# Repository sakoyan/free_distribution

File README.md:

# free_distribution
free circuit data for robocon

おでんの基板データ配布場所です。
一応完成版がアップされると思いますし、動作もすると思います。
不備などを見つけた方は@oden_umaruにビシバシとリプを飛ばしてください。
今までのデータを順次公開していきたいと思います。

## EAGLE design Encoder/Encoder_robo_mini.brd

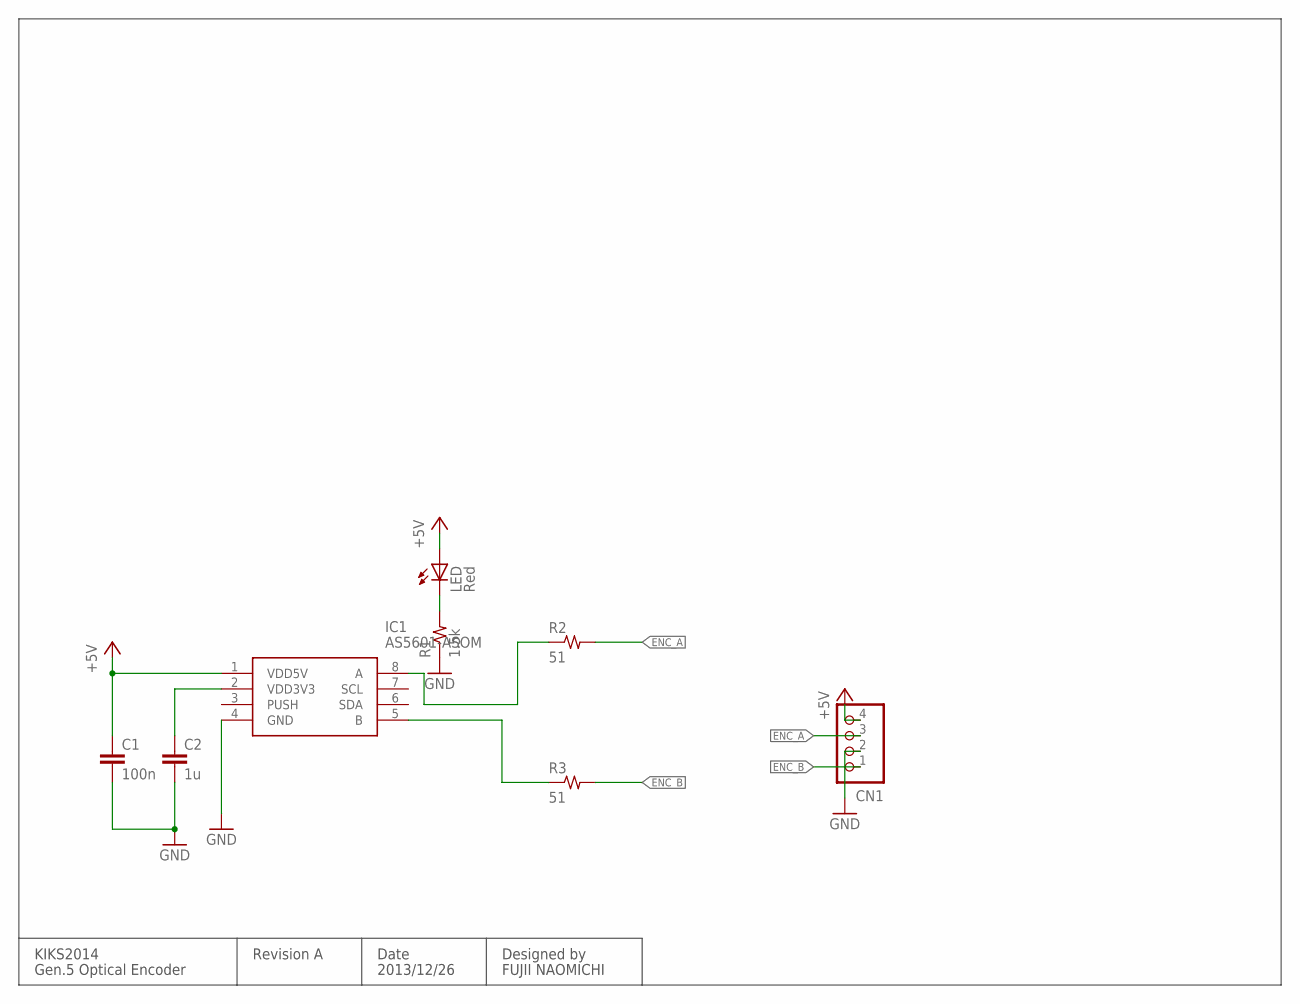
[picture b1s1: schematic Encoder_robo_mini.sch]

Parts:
C1: 100n; 1608
C2: 1u; 1608
CN1: S4B-XH-A
IC1: AS5601-ASOM; SOIC127P600X175-8N
LED: Red; LED3MM
R1: 1.5k; 1608
R2, R3: 51; 1608

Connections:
+5V: C1.1, CN1.4, IC1.1 (VDD5V), LED.A
ENC_A: CN1.3, R2.2
ENC_B: CN1.1, R3.2
GND: C1.2, C2.2, CN1.2, IC1.4 (GND), R1.1
unnamed: IC1.8 (A), R2.1
unnamed: C2.1, IC1.2 (VDD3V3)
unnamed: IC1.5 (B), R3.1
unnamed: LED.K (C), R1.2

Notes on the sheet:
KIKS2014
Gen.5 Optical Encoder
FUJII NAOMICHI
Designed by
Date
2013/12/26
Revision A

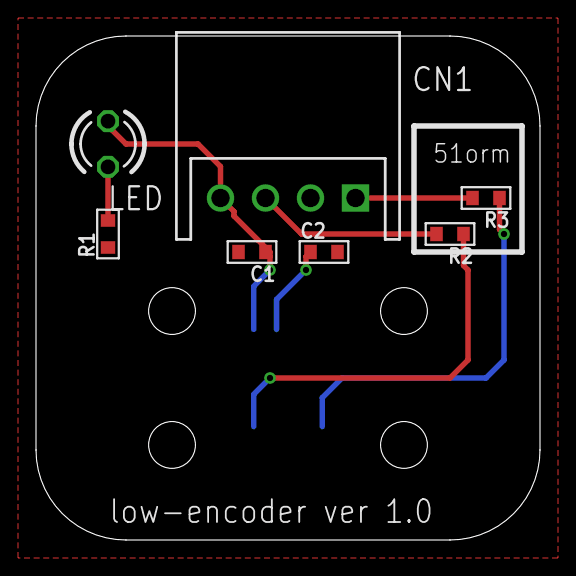
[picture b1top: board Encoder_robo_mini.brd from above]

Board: 2 copper layers, 28.0 x 28.0 mm, 8 parts (1 on the bottom side), 8 nets.

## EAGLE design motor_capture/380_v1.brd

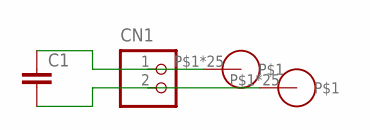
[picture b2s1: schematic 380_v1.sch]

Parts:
C1: C-EUC1608; C1608
CN1: B2P-VH
U$1, U$2: MOTOR_PIN2; PAD_PIN

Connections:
unnamed: C1.1, CN1.1, U$1.P$1, U$1.P$2, U$1.P$3, U$1.P$4, U$1.P$5, U$1.P$6, U$1.P$7, U$1.P$8, U$1.P$9, U$1.P$10, U$1.P$11, U$1.P$12, U$1.P$13, U$1.P$14, U$1.P$15, U$1.P$16, U$1.P$17, U$1.P$18, U$1.P$19, U$1.P$20, U$1.P$21, U$1.P$22, U$1.P$23, U$1.P$24, U$1.P$25
unnamed: C1.2, CN1.2, U$2.P$1, U$2.P$2, U$2.P$3, U$2.P$4, U$2.P$5, U$2.P$6, U$2.P$7, U$2.P$8, U$2.P$9, U$2.P$10, U$2.P$11, U$2.P$12, U$2.P$13, U$2.P$14, U$2.P$15, U$2.P$16, U$2.P$17, U$2.P$18, U$2.P$19, U$2.P$20, U$2.P$21, U$2.P$22, U$2.P$23, U$2.P$24, U$2.P$25

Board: 2 copper layers, 4 parts (0 on the bottom side), 2 nets, no tracks yet.

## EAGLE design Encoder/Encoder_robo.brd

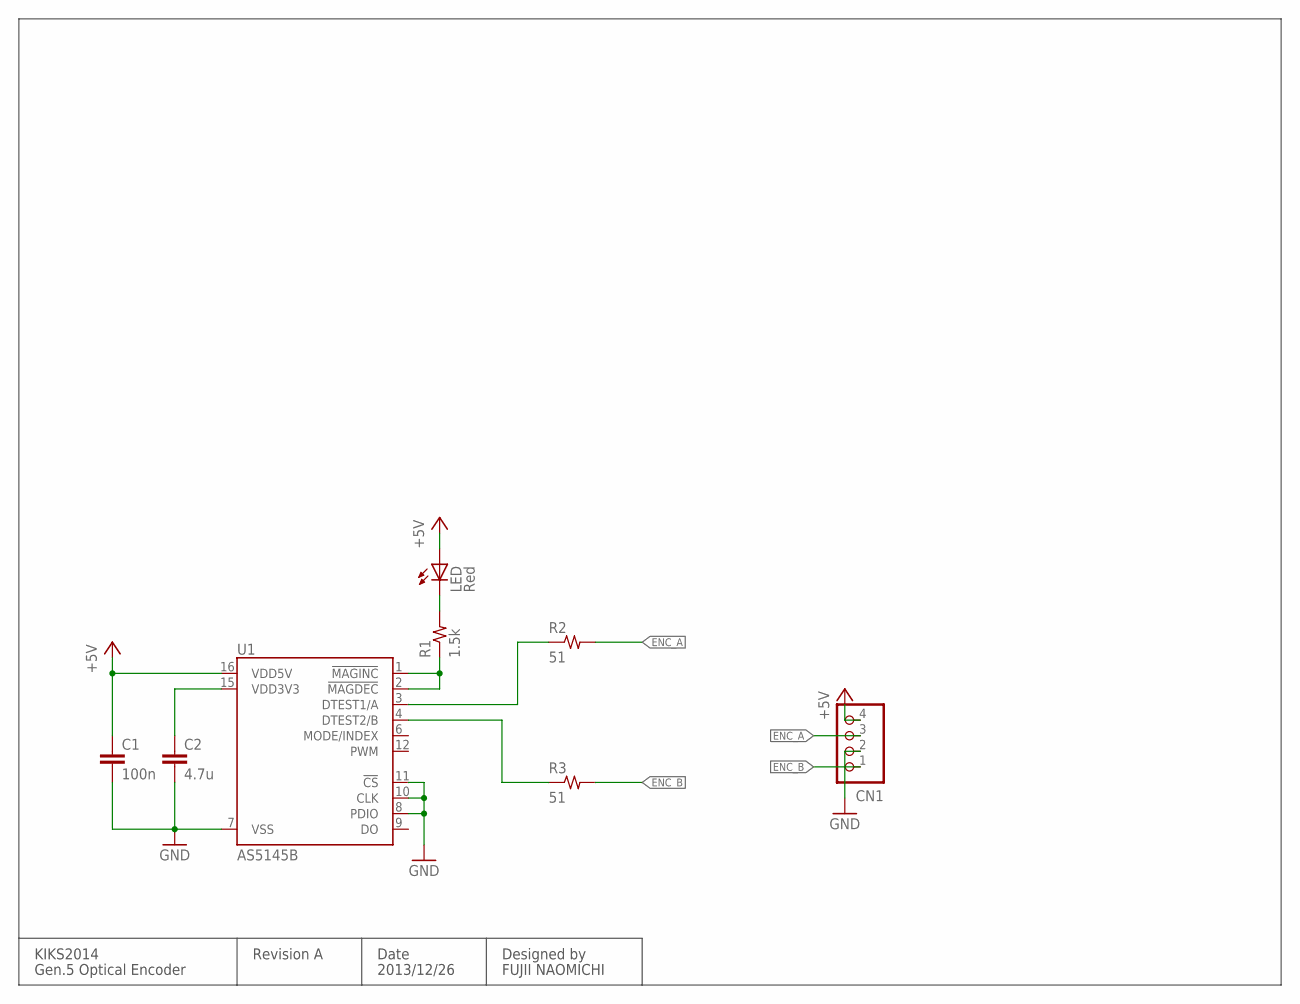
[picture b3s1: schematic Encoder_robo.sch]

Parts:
C1: 100n; 1608
C2: 4.7u; 1608
CN1: S4B-XH-A
LED: Red; LED3MM
R1: 1.5k; 1608
R2, R3: 51; 1608
U1: AS5145B; SSOP16

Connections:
+5V: C1.1, CN1.4, LED.A, U1.16 (VDD5V)
ENC_A: CN1.3, R2.2
ENC_B: CN1.1, R3.2
GND: C1.2, C2.2, CN1.2, U1.7 (VSS), U1.8 (PDIO), U1.10 (CLK), U1.11 (!CS)
unnamed: R2.1, U1.3 (DTEST1/A)
unnamed: C2.1, U1.15 (VDD3V3)
unnamed: R3.1, U1.4 (DTEST2/B)
unnamed: LED.K (C), R1.2
unnamed: R1.1, U1.1 (!MAGINC), U1.2 (!MAGDEC)

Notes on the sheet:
KIKS2014
Gen.5 Optical Encoder
FUJII NAOMICHI
Designed by
Date
2013/12/26
Revision A

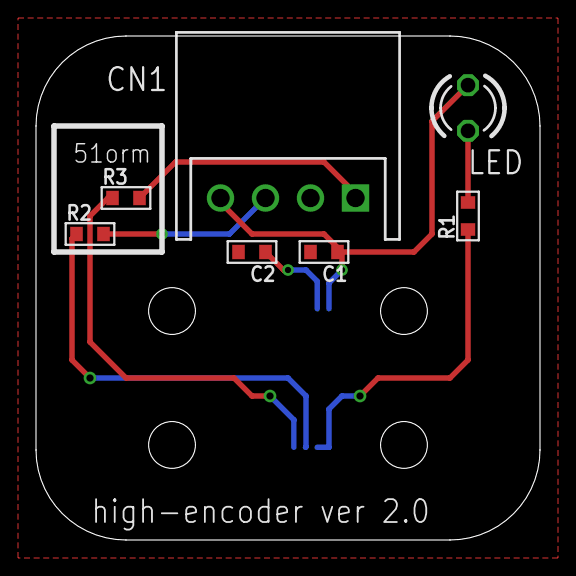
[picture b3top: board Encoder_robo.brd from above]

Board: 2 copper layers, 28.0 x 28.0 mm, 8 parts (1 on the bottom side), 9 nets.

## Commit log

2018-04-21 エンコーダーとモーターマウントの追加
